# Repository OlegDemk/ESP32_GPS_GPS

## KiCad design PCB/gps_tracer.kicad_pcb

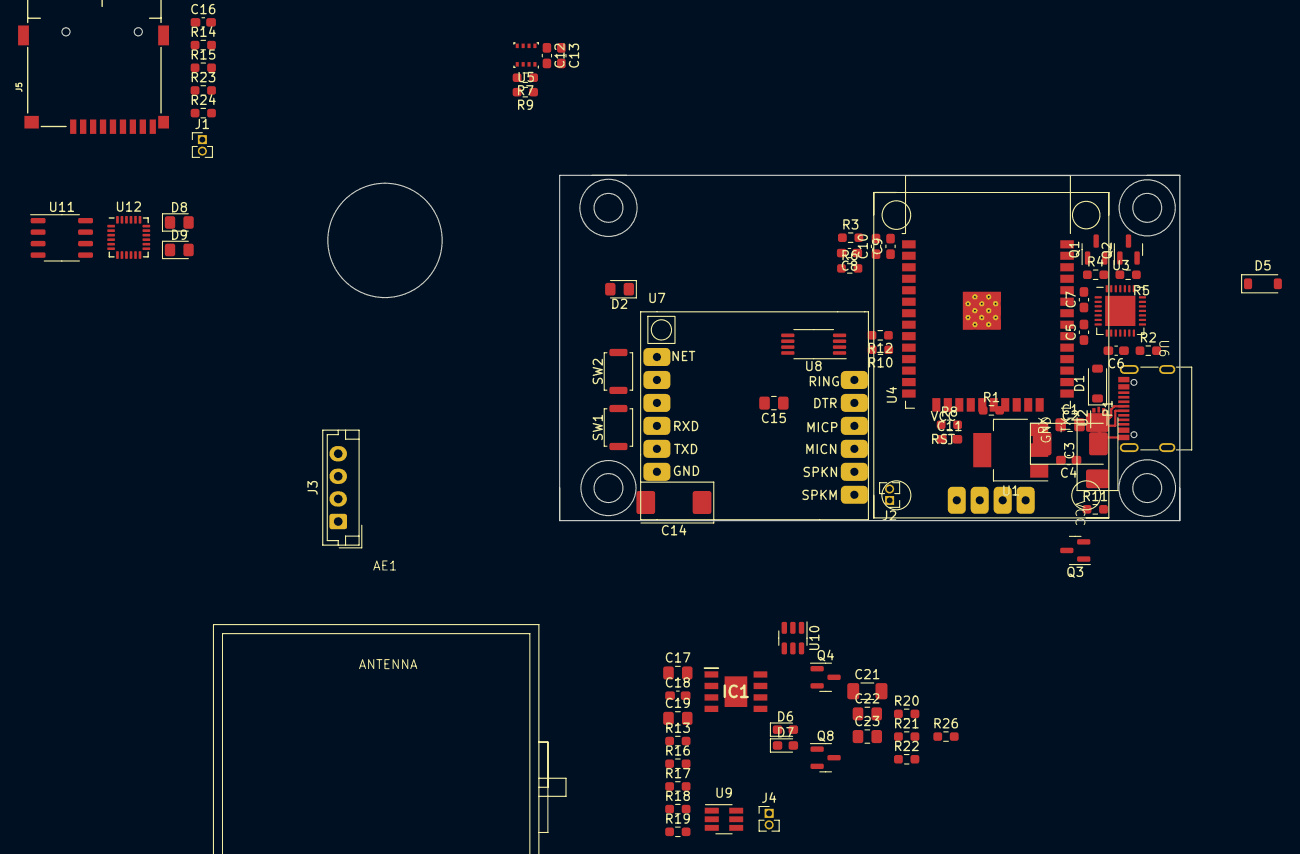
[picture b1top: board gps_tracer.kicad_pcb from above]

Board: 2 copper layers, 94.2 x 38.2 mm, 85 parts (0 on the bottom side), 60 nets.

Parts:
AE1: Antenna; GPS_ANTENNA
C1, C15, C22, C23: 22u; C_0805_2012Metric_Pad1.18x1.45mm_HandSolder
C2, C3, C14: 470u; CP_EIA-7343-31_Kemet-D
C4, C5, C6, C8, C10, C11, C12, C13: 100n; C_0603_1608Metric_Pad1.08x0.95mm_HandSolder
C7: 47u; C_0603_1608Metric_Pad1.08x0.95mm_HandSolder
C9: 22u; C_0603_1608Metric_Pad1.08x0.95mm_HandSolder
C16, C18: 100nF; C_0603_1608Metric_Pad1.08x0.95mm_HandSolder
C17, C19: 16uF; C_0805_2012Metric_Pad1.18x1.45mm_HandSolder
C21: 100u; C_1206_3216Metric_Pad1.33x1.80mm_HandSolder
D1, D5: BAT48ZFILM; D_SOD-123
D2, D8, D9: LED; LED_0805_2012Metric_Pad1.15x1.40mm_HandSolder
D6: LED Charging red; LED_0603_1608Metric_Pad1.05x0.95mm_HandSolder
D7: LED Full blue; LED_0603_1608Metric_Pad1.05x0.95mm_HandSolder
H1, H2, H3, H4: MountingHole; MountingHole_2.2mm_M2
IC1: TC4056A; SOIC127P600X175-9N
J1: Mic; PinHeader_1x02_P1.27mm_Vertical
J2: SPK; PinHeader_1x02_P1.27mm_Vertical
J3: sensor; JST_EH_B4B-EH-A_1x04_P2.50mm_Vertical
J4: BATTERY; PinHeader_1x02_P1.27mm_Vertical
J5: Micro_SD_Card; J_SD_Card-micro_socket_A (1)
P1: USB_C_Plug_USB2.0; USB_C_Receptacle_G-Switch_GT-USB-7010ASV
Q1, Q2: S8050; SOT-23
Q3, Q8: FDN358P; SOT-23
Q4: LTC4412; SOT-23
R1, R19, R23: 700; R_0603_1608Metric_Pad0.98x0.95mm_HandSolder
R2: 2k; R_0603_1608Metric_Pad0.98x0.95mm_HandSolder
R3, R4, R5, R10, R12, R22, R24: 10k; R_0603_1608Metric_Pad0.98x0.95mm_HandSolder
R6, R8: 470; R_0603_1608Metric_Pad0.98x0.95mm_HandSolder
R7, R9: 4.7k; R_0603_1608Metric_Pad0.98x0.95mm_HandSolder
R11, R26: 9k; R_0603_1608Metric_Pad0.98x0.95mm_HandSolder
R13, R16, R18: 1k; R_0603_1608Metric_Pad0.98x0.95mm_HandSolder
R14: 100; R_0603_1608Metric_Pad0.98x0.95mm_HandSolder
R15: 470k; R_0603_1608Metric_Pad0.98x0.95mm_HandSolder
R17: 1200; R_0603_1608Metric_Pad0.98x0.95mm_HandSolder
R20: 30k; R_0603_1608Metric_Pad0.98x0.95mm_HandSolder
R21: 73.2k; R_0603_1608Metric_Pad0.98x0.95mm_HandSolder
SW1: EN; SW_Push_SPST_NO_Alps_SKRK
SW2: BOOT; SW_Push_SPST_NO_Alps_SKRK
U1: AMS1117-3.3; SOT-223-3_TabPin2
U2: USBLC6-2P6; SOT-666
U3: CP2102N-Axx-xQFN28; QFN-28-1EP_5x5mm_P0.5mm_EP3.35x3.35mm
U4: ESP32-WROOM-32
U5: BME280; Bosch_LGA-8_2.5x2.5mm_P0.65mm_ClockwisePinNumbering
U6: GY_GPS6MV2_module
U7: SIM800L-CORE
U8: FS8205A; TSSOP-8_4.4x3mm_P0.65mm
U9: DW01A; SOT-23-6_Handsoldering
U10: LTC4412xS6; TSOT-23-6
U11: FP6298; SOP-8_3.9x4.9mm_P1.27mm
U12: MPU-6050; InvenSense_QFN-24_4x4mm_P0.5mm

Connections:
+3.3V: C1.1, C3.1, C4.1, C6.1, C7.1, C9.1, C10.1, C12.1, C13.1, C16.1, J3.3, J5.4 (VSS), Q3.2 (S), R2.1, R3.1, R7.1, R9.1, R10.2, R11.2, R12.2, R24.2, U1.2 (VO), U3.6 (VDD), U3.7 (VREGIN), U4.2 (VDD), U5.2 (CSB), U5.5 (SDO), U5.6 (VDDIO), U5.8 (VDD)
+5V: C5.1, C19.1, D1.2 (A), D6.2 (A), D7.2 (A), IC1.4 (VCC), IC1.8 (CE), P1.A4 (VBUS), P1.A9 (VBUS), P1.B4 (VBUS), P1.B9 (VBUS), R15.1, U2.5 (VBUS), U3.8 (VBUS), U10.6 (SENSE)
BLUE_LED: R1.1, U4.9 (IO33)
DTR: Q2.2 (E), R4.2, U3.28 (~DTR)
DTS: Q1.2 (E), R5.2, U3.24 (~RTS)
EN: Q1.3 (C), R6.1, U4.3 (EN)
GND: C1.2, C2.2, C3.2, C4.2, C5.2, C6.2, C7.2, C8.2, C9.2, C10.2, C11.2, C12.2, C13.2, C14.2, C15.2, C16.2, C17.2, C19.2, C21.2, C22.2, C23.2, D2.1 (K), D8.1 (K), D9.1 (K), IC1.1 (TEMP), IC1.3 (GND), J3.4, J5.6 (VDD), P1.A1 (GND), P1.A12 (GND), P1.B1 (GND), P1.B12 (GND), R17.1, R18.1, R20.1, R22.1, SW1.1, SW2.2, U1.1 (GND), U2.2 (GND), U3.3 (GND), U3.29 (GND), U4.1 (GND), U4.15 (GND), U4.38 (GND), U4.39 (GND), U5.1 (GND), U5.7 (GND), U6.4 (GND), U7.6 (GND), U8.6 (S2), U8.7 (S2), U10.2 (GND), U10.3 (CTL), U11.1 (PGND), U11.5 (GND)
GPS_RX: U4.28 (IO17), U6.2 (RX)
GPS_TX: U4.27 (IO16), U6.3 (TX)
GREEN_LED: R19.1, U4.10 (IO25)
GSM_POWER_SOURSE: C22.1, C23.1, D5.1 (K), Q8.2 (S), R21.2, R26.2, U1.3 (VI)
IO0: Q2.3 (C), R8.2, U4.25 (IO0)
MICROSD_CLK: J5.5 (CLK), U4.13 (IO14)
MICROSD_CS: J5.2 (DAT1), R24.1, U4.16 (IO13)
MICROSD_MISO: J5.7 (CMD), R12.1, U4.31 (IO19)
MICROSD_MOSI: J5.3 (DAT0), R10.1, U4.37 (IO23)
unnamed: C8.1, R3.2, R6.2, SW1.2
unnamed: C11.1, R8.1, SW2.1
unnamed: C15.1, C21.1, D1.1 (K), Q4.2 (S), U11.3 (Vcc), U11.4 (EN)
unnamed: D2.2 (A), R1.2
unnamed: D5.2 (A), U11.8 (LX)
unnamed: D6.1 (K), R13.2
unnamed: D7.1 (K), R16.2
unnamed: D8.2 (A), R19.2
unnamed: D9.2 (A), R23.2
unnamed: C17.1, C18.1, IC1.5 (BAT), Q4.3 (D), R14.2, U9.5 (VCC), U10.1 (VIN)
unnamed: IC1.7 (CHRG), R13.1
unnamed: IC1.2 (PROG), R17.2
unnamed: IC1.6 (STDBY), R16.1
unnamed: J1.1, U7.9 (MICN)
unnamed: J1.2, U7.10 (MICP)
unnamed: J2.1, U7.7 (SPKM)
unnamed: J2.2, U7.8 (SPKN)
unnamed: C18.2, J4.1, U8.2 (S1), U8.3 (S1), U9.6 (GND)
unnamed: J4.2, R14.1
unnamed: P1.A6 (D+), U2.3 (I/O2)
unnamed: P1.A7 (D-), U2.1 (I/O1)
unnamed: Q1.1 (B), R4.1
unnamed: Q2.1 (B), R5.1
unnamed: Q3.3 (D), U6.1 (VCC)
unnamed: Q4.1 (G), U10.5 (GATE)
unnamed: C2.1, C14.1, Q8.3 (D), U7.2 (VCC)
unnamed: U2.4 (I/O2), U3.4 (D+)
unnamed: U2.6 (I/O1), U3.5 (D-)
unnamed: R2.2, U3.9 (~RST)
unnamed: R18.2, U9.2 (CS)
unnamed: R15.2, U10.4 (STAT)
unnamed: R21.1, R22.2, U11.6 (FB)
unnamed: R20.2, U11.2 (OC)
OC: U8.5 (G2), U9.3 (OC)
OD: U8.4 (G1), U9.1 (OD)
POWER_OF_GPS: Q3.1 (G), R11.1, U4.11 (IO26)
POWER_OF_GSM: Q8.1 (G), R26.1, U4.12 (IO27)
RED_LED: R23.1, U4.30 (IO18)
RXD: U3.26 (TXD), U4.34 (RXD0/IO3)
RXD_GSM: U4.23 (IO15), U7.4 (RXD)
SCL: J3.2, R9.2, U4.36 (IO22), U5.4 (SCK), U12.23 (SCL)
SDA: J3.1, R7.2, U4.33 (IO21), U5.3 (SDI), U12.24 (SDA)
TXD: U3.25 (RXD), U4.35 (TXD0/IO1)
TXD_GSM: U4.29 (IO5), U7.5 (TXD)

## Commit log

2024-03-23 add some
2024-04-03 The PCB was traced, and ordered
